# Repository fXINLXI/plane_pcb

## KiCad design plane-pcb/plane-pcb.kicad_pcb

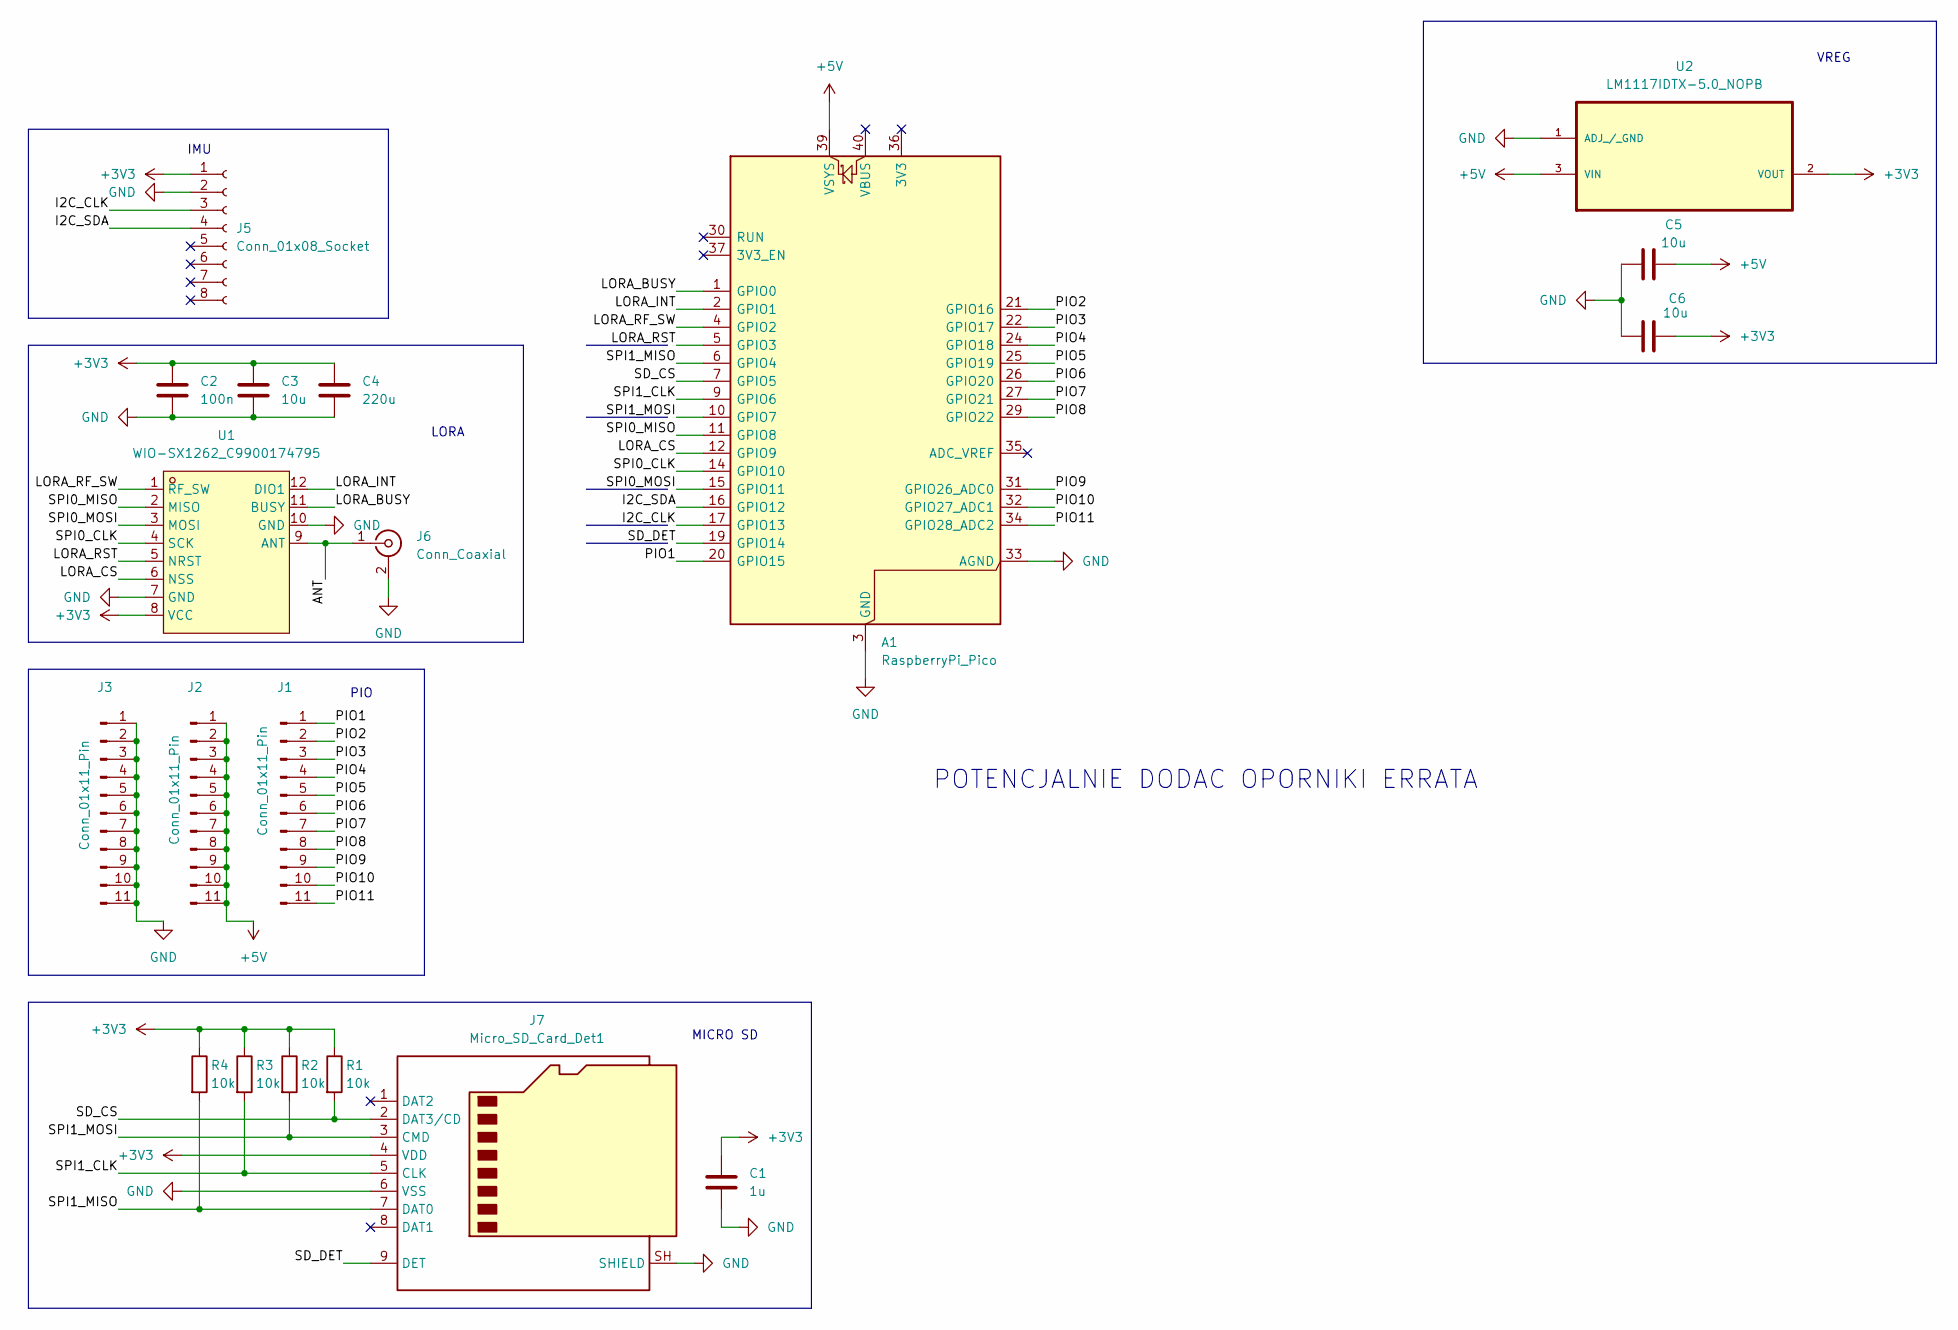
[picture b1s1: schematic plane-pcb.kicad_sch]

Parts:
A1: RaspberryPi_Pico; RaspberryPi_Pico_Plain
C1: 1u; C_0603_1608Metric_Pad1.08x0.95mm_HandSolder
C2: 100n; C_0603_1608Metric_Pad1.08x0.95mm_HandSolder
C3, C5, C6: 10u; C_0603_1608Metric_Pad1.08x0.95mm_HandSolder
C4: 220u; CP_Radial_D5.0mm_P2.00mm
J1, J2, J3: Conn_01x11_Pin; PinHeader_1x11_P2.54mm_Vertical
J5: Conn_01x08_Socket; PinHeader_1x08_P2.54mm_Vertical
J6: Conn_Coaxial; SMA_Amphenol_132134-14_Vertical
J7: Micro_SD_Card_Det1; J_SD_Card-micro_socket_A
R1, R2, R3, R4: 10k; R_0805_2012Metric_Pad1.20x1.40mm_HandSolder
U1: WIO-SX1262_C9900174795; WIO-SX1262; MPN Wio-SX1262; LCSC Part C9900174795
U2: LM1117IDTX-5.0_NOPB; TO228P970X238-3N; MPN LM1117IDTX-5.0/NOPB

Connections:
+3V3: C1.1, C2.1, C3.1, C4.1, C6.2, J5.1, J7.4 (VDD), R1.1, R2.1, R3.1, R4.1, U1.8 (VCC), U2.2 (VOUT)
+5V: A1.39 (VSYS), C5.2, J2.1, J2.2, J2.3, J2.4, J2.5, J2.6, J2.7, J2.8, J2.9, J2.10, J2.11, U2.3 (VIN)
/ANT: J6.1 (In), U1.9 (ANT)
/I2C_CLK: A1.17 (GPIO13), J5.3
/I2C_SDA: A1.16 (GPIO12), J5.4
/LORA_BUSY: A1.1 (GPIO0), U1.11 (BUSY)
/LORA_CS: A1.12 (GPIO9), U1.6 (NSS)
/LORA_INT: A1.2 (GPIO1), U1.12 (DIO1)
/LORA_RF_SW: A1.4 (GPIO2), U1.1 (RF_SW)
/LORA_RST: A1.5 (GPIO3), U1.5 (NRST)
/PIO1: A1.20 (GPIO15), J1.1
/PIO2: A1.21 (GPIO16), J1.2
/PIO3: A1.22 (GPIO17), J1.3
/PIO4: A1.24 (GPIO18), J1.4
/PIO5: A1.25 (GPIO19), J1.5
/PIO6: A1.26 (GPIO20), J1.6
/PIO7: A1.27 (GPIO21), J1.7
/PIO8: A1.29 (GPIO22), J1.8
/PIO9: A1.31 (GPIO26_ADC0), J1.9
/PIO10: A1.32 (GPIO27_ADC1), J1.10
/PIO11: A1.34 (GPIO28_ADC2), J1.11
/SD_CS: A1.7 (GPIO5), J7.2 (DAT3/CD), R1.2
/SD_DET: A1.19 (GPIO14), J7.9 (DET)
/SPI0_CLK: A1.14 (GPIO10), U1.4 (SCK)
/SPI0_MISO: A1.11 (GPIO8), U1.2 (MISO)
/SPI0_MOSI: A1.15 (GPIO11), U1.3 (MOSI)
/SPI1_CLK: A1.9 (GPIO6), J7.5 (CLK), R3.2
/SPI1_MISO: A1.6 (GPIO4), J7.7 (DAT0), R4.2
/SPI1_MOSI: A1.10 (GPIO7), J7.3 (CMD), R2.2
GND: A1.3 (GND), A1.8 (GND), A1.13 (GND), A1.18 (GND), A1.23 (GND), A1.28 (GND), A1.33 (AGND), A1.38 (GND), C1.2, C2.2, C3.2, C4.2, C5.1, C6.1, J3.1, J3.2, J3.3, J3.4, J3.5, J3.6, J3.7, J3.8, J3.9, J3.10, J3.11, J5.2, J6.2 (Ext), J7.6 (VSS), J7.SH (SHIELD), U1.7 (GND), U1.10 (GND), U2.1 (ADJ_/_GND)

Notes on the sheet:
MICRO SD
IMU
VREG
LORA
PIO
POTENCJALNIE DODAC OPORNIKI ERRATA

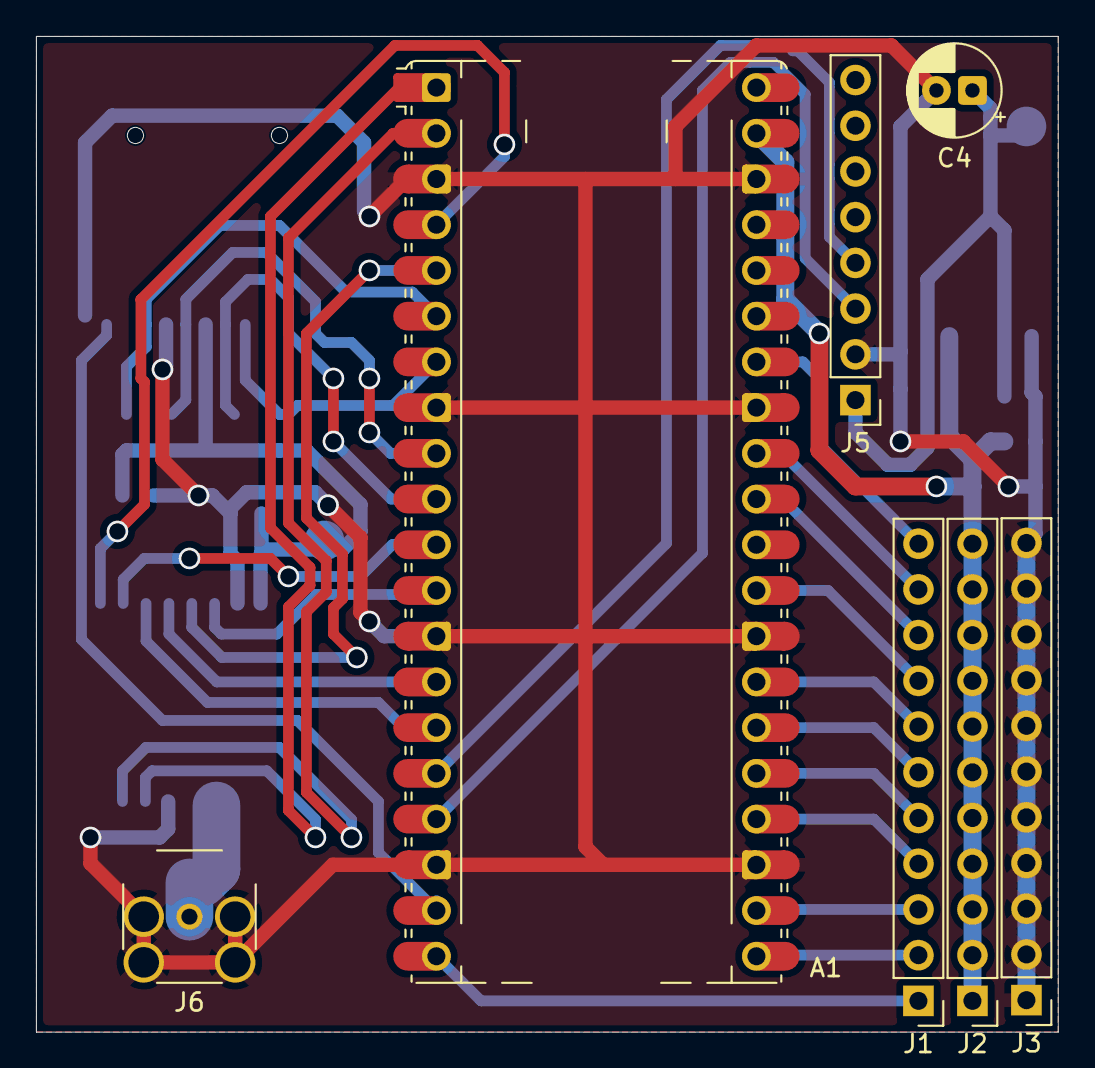
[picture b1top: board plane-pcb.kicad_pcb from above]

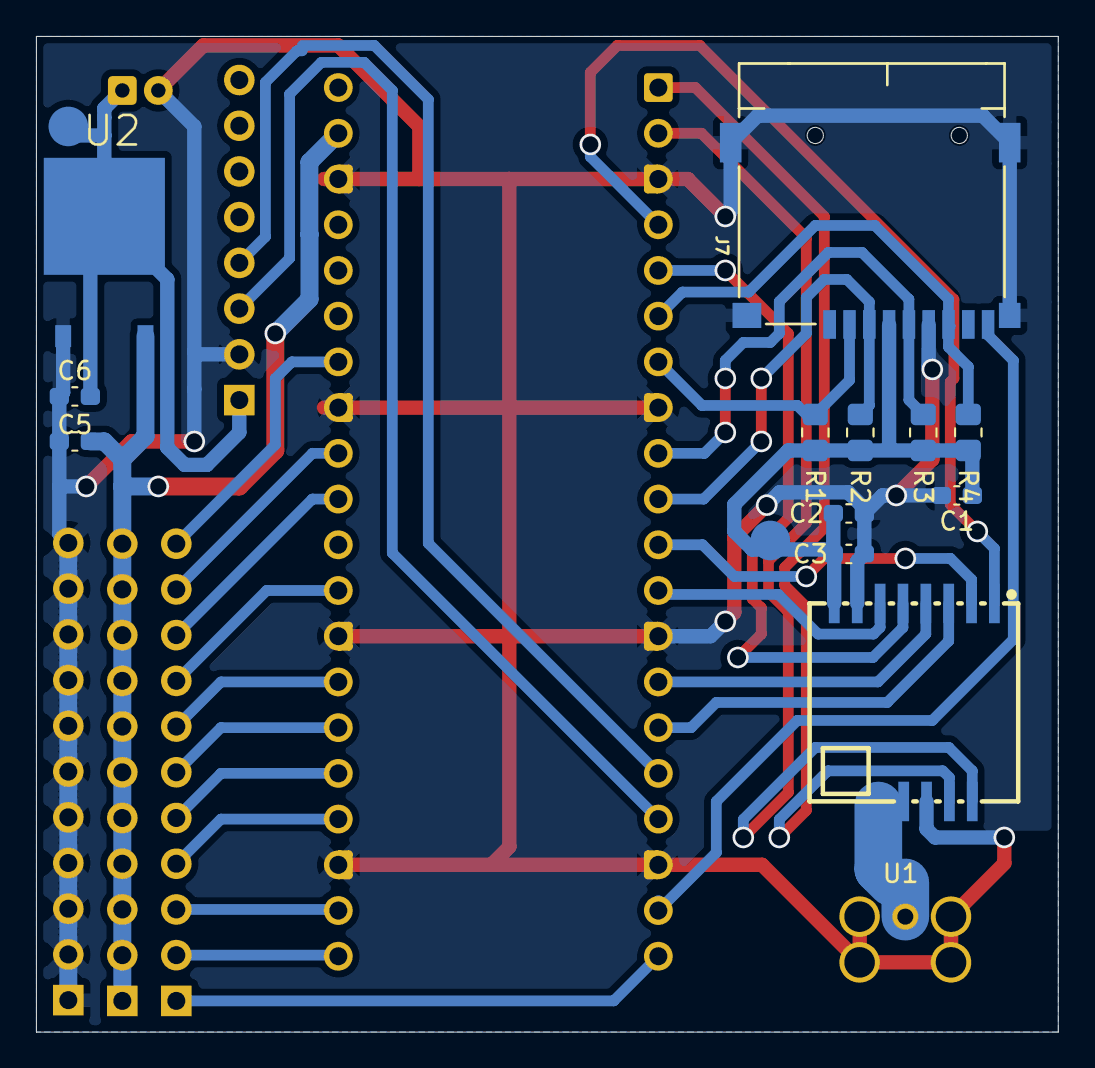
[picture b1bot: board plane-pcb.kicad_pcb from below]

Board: 2 copper layers, 56.8 x 55.3 mm, 19 parts (12 on the bottom side), 30 nets.
